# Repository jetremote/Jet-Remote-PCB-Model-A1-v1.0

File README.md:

# Jet-Remote-PCB-Model-A1-v1.0
Jet Remote Receiver

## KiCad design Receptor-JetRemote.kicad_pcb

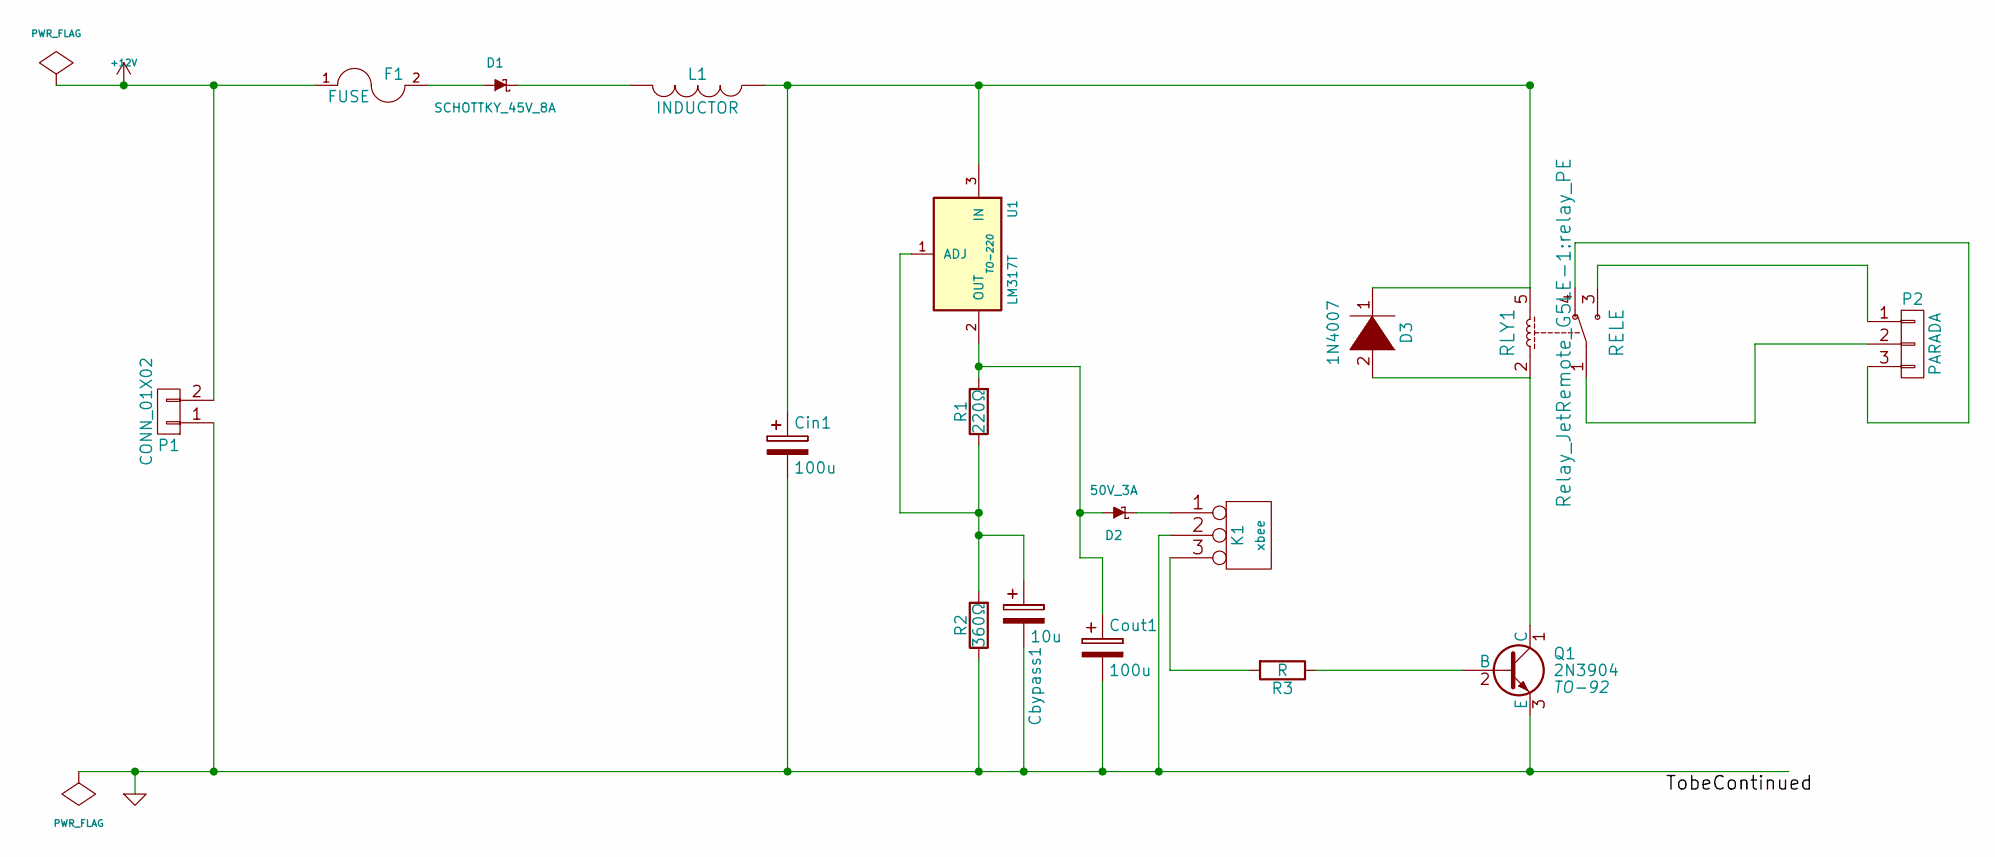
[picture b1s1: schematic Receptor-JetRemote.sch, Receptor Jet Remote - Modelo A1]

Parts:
Cbypass1: 10u
Cin1: 100u
Cout1: 100u
D1: SCHOTTKY_45V_8A
D2: 50V_3A
D3: 1N4007
F1: FUSE
K1: xbee
L1: INDUCTOR
P1: CONN_01X02
P2: PARADA
Q1: 2N3904; TO-92
R1: 220Ω
R2: 360Ω
R3: R
RLY1: RELE; relay_PE
U1: LM317T; TO-220

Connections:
+12V: F1.1, P1.2
GND: Cbypass1.2, Cin1.2, Cout1.2, K1.2 (PM), P1.1, Q1.3 (E), R2.1
unnamed: Cbypass1.1, R1.1, R2.2, U1.1 (ADJ)
unnamed: Cin1.1, D3.1 (K), L1.1, RLY1.5, U1.3 (IN)
unnamed: Cout1.1, D2.1 (A), R1.2, U1.2 (OUT)
unnamed: D1.1 (A), F1.2
unnamed: D1.2 (K), L1.2
unnamed: D2.2 (K), K1.1
unnamed: D3.2 (A), Q1.1 (C), RLY1.2
unnamed: K1.3, R3.2
unnamed: P2.1, RLY1.3
unnamed: P2.2, RLY1.1
unnamed: P2.3, RLY1.4
unnamed: Q1.2 (B), R3.1

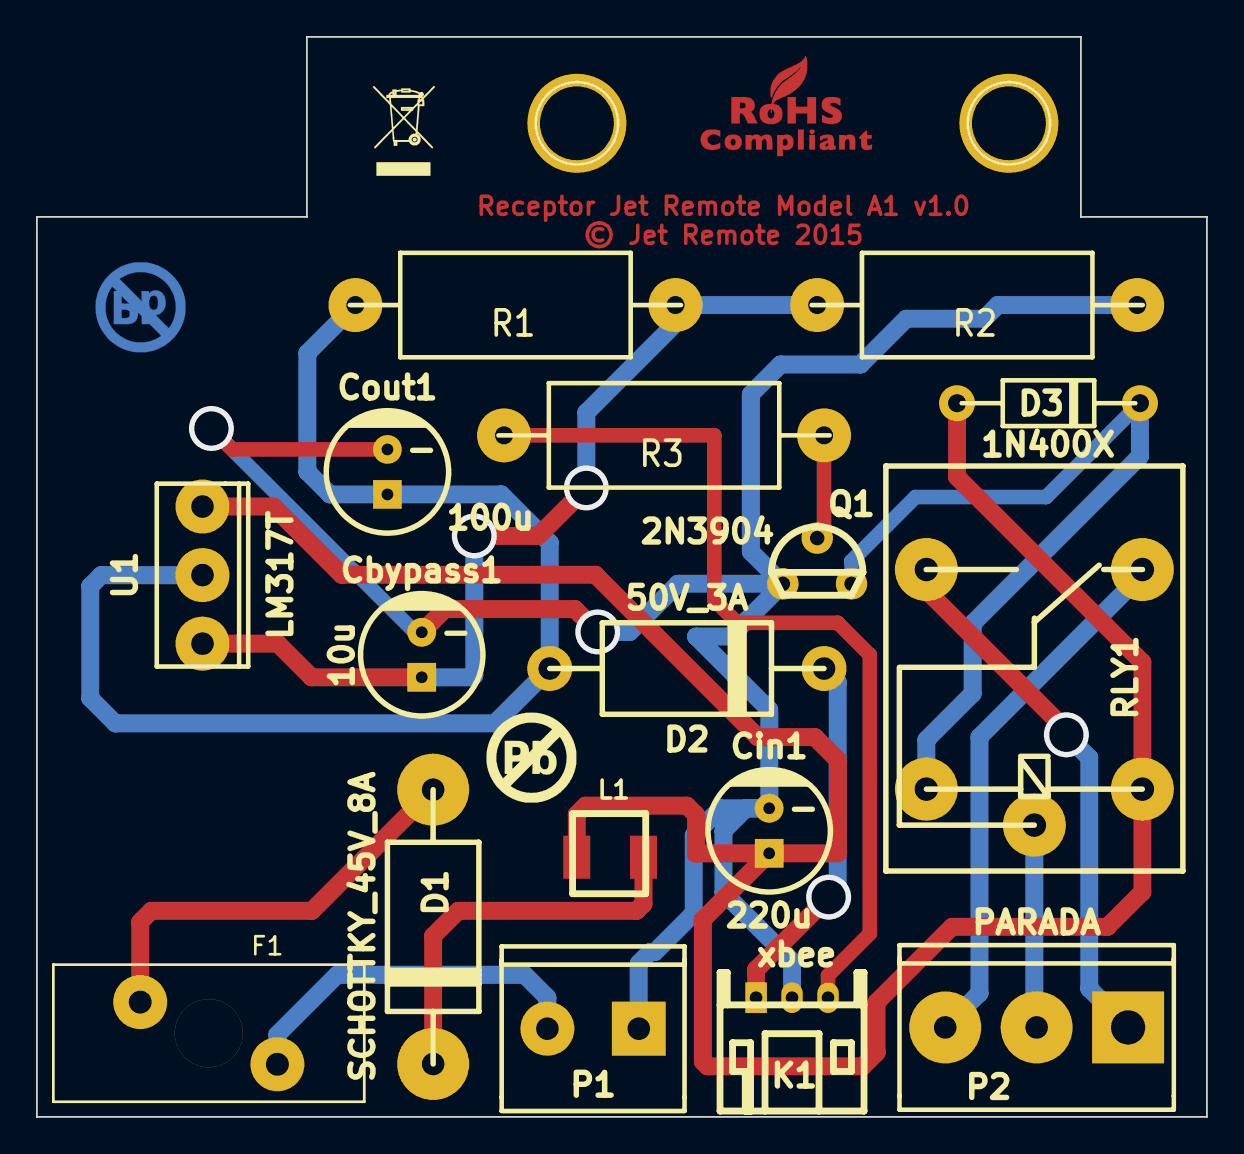
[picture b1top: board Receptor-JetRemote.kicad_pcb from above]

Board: 2 copper layers, 65.0 x 60.0 mm, 17 parts (0 on the bottom side), 14 nets.

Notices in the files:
Receptor-JetRemote.kicad_pcb:
© Jet Remote 2015
Receptor-JetRemote.sch:
GPL v3
